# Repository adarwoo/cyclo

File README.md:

# cyclo
Author: Guillaume (Bill) ARRECKX

Brief
=====
Cyclo is a remote controllable relay capable of handling 16A over 240V AC or 3A over 120V DC.
It is housed in a DIN mountable enclosure, and offers 2 banana sockets as well as Molex connection.
It is powered through a USB socket, which also allow to drive it remotely, using a VT100 terminal.
It features a small OLED screen and a joystick to drive it manually, and display operation stats.

Intro
=====
As a professional embedded software architect, I always work on small pet
projects to keep myself up-to-date with the latest changes in languages.
This project was the perfect excuse to get to try the latest C++20 features.
Using a small, resource constrained microcontroller, is far more very
revealing of the compilers performance. 

The project initially tried to create a meta modelled framework (using concepts et al.), but
the effort required, the debug, the maintenability did not seem reasonable for now. C++20 brings
many good things, but they perform best in libraries, and should not be used solely because they
exist and are new! I also had some issues compiling existing code, so in the end, I downgraded
the project to a C++17 compiler.

Nontheless, the project features many interesting features, such as:
 * An AVR xMega (ATxMega128A4U) with 128K of flash and 8K of RAM, 2K of EEProm and a USB port
 * A XMega port of the latest FreeRTOS (10.4.4)
 * A C++ wrapper for FreeRTOS (home brew using typestrings from https://github.com/irrequietus/typestring)
 * The excellent ETL library https://www.etlcpp.com/ (I added a Tokenizer class)
 * A message framework (on top of ETL messages and FreeRTOS queues)
 * The boost::sml state machine library

Product description
===================
Cyclo can be used to cycle some systems on/off many times to validate proper boot up of embedded
equipments. It can be used to turn on/off any devices, down to 10ms to test power supplies resilence for example.
The remote control and computer friendly, and allow to control the relay directly.

The system can start automatically too.

The joystick on the side, allow configuring Cyclo manually to create a simple repeating on/off program,
with timings from 1 second to 100 minutes - on and off.

The toggle switch allow to make it normally opened or close when powered off or idle.

Up to 10 programs can be created for different scenari, single run, or repeating sequences.
When driving it from a computer, it is possible to create some custom profiles,
using random numbers, or ramps to vary the timing to look for a specific problem.

Software
========
The software architecture was done in UML, with class diagram, sequence diagram and state machines.
The emphasis is on using as much C++ as required.

No dynamic memory is used - and the stack is used as little as possible.

Building the software
=====================
The software has been written for a gcc C++17 compiler. It can be compiled
for an AVR xMega, or for a Linux PC, to run the simulator.
The need for the simulator is to allow proper debugging, which is not
possible using the Microchip Studio since the latest supported compiler is
a gcc 4.7 (the latest at the time of writting this is the 11), but to get
the c++17 feature, the compiler must be updated, and the debugging no
longer works correctly.
A makefile is also provided to compile in Linux or WSL2.
Since it uses a recent compiler, I have added a Dockerfile to create a container
to rebuild all. If you're running Linux or Windows 10/11, use the Docker container
and save yourselve plenty of pain.
A convenient script will build the docker container and launch the build.
The layout keeps the Microchip Studio layout - which is not ideal IMHO. The project can
still be opened with Microchip studio - but you'll need to ugrade the compiler.
A makefile is added to build from the command line.
The format of the files is managed by clang-format-10 which the clang config
file added.
Note: Gcc 8 or greater is required. I am using gcc 11.
I use Microsoft VSCode for all the developement - including debugging (the simulated version).
I find it is a fantastic IDE with none of the Eclipse heavyness and frustrations.
The .vs workspace is part of the distribution.

Building the hardware
=====================
The PCB can be done as a single or double sided !
Cyclo has been designed with an old Cadsoft Eagle (v7.x) using a non-profile licence.
Since, CadSoft was acquired by Autodesk, but the files remain compatible with
the latest version of Eagle. Given the size of the PCB, the free edition is enough.

I have added the .brd and .sch which must PCB house will take.
If you plan on making the PCB yourself - you will need a production method which can achieve 
at least 10mil tracks and isolation. A good CNC will do that. If you're etching, you absolutly need to
know what you're doing. This is the top end of home made PCBs, but poeple with experience can do it.
I personnaly still etch my PCB and also do PTH (Yes!). But I have a CNC for drilling, and 
a lot of chemicals like paladium... and 15 years experience doing it.

Building the case
=================
The case was designed with open source CAD and is made available as 
STL and STEP. It is 3D printer friendly.
I use a Prusa MK3 with PLA or PETG.
The PCB once cut to size will clip in place. No screews required.

Licence
=======
Cyclo is licenced under MIT licence.

External links
==============

* FreeRTOS              : https://freertos.org
* ETL                   : https://www.etlcpp.com
* Boost SML             : https://boost-ext.github.io/sml/index.html
* Typestring library    : https://github.com/irrequietus/typestring
* Toolchain for Windows : https://blog.zakkemble.net/avr-gcc-builds/
* Toolchain for Linux   : https://avr.lumito.net/downloads/
* Docker                : https://www.docker.com
* VSCode                : https://code.visualstudio.com
* Git                   : https://git-scm.com
* GNU Make              : https://www.gnu.org/software/make/
* Eagle                 : https://www.autodesk.fr/products/eagle/overview

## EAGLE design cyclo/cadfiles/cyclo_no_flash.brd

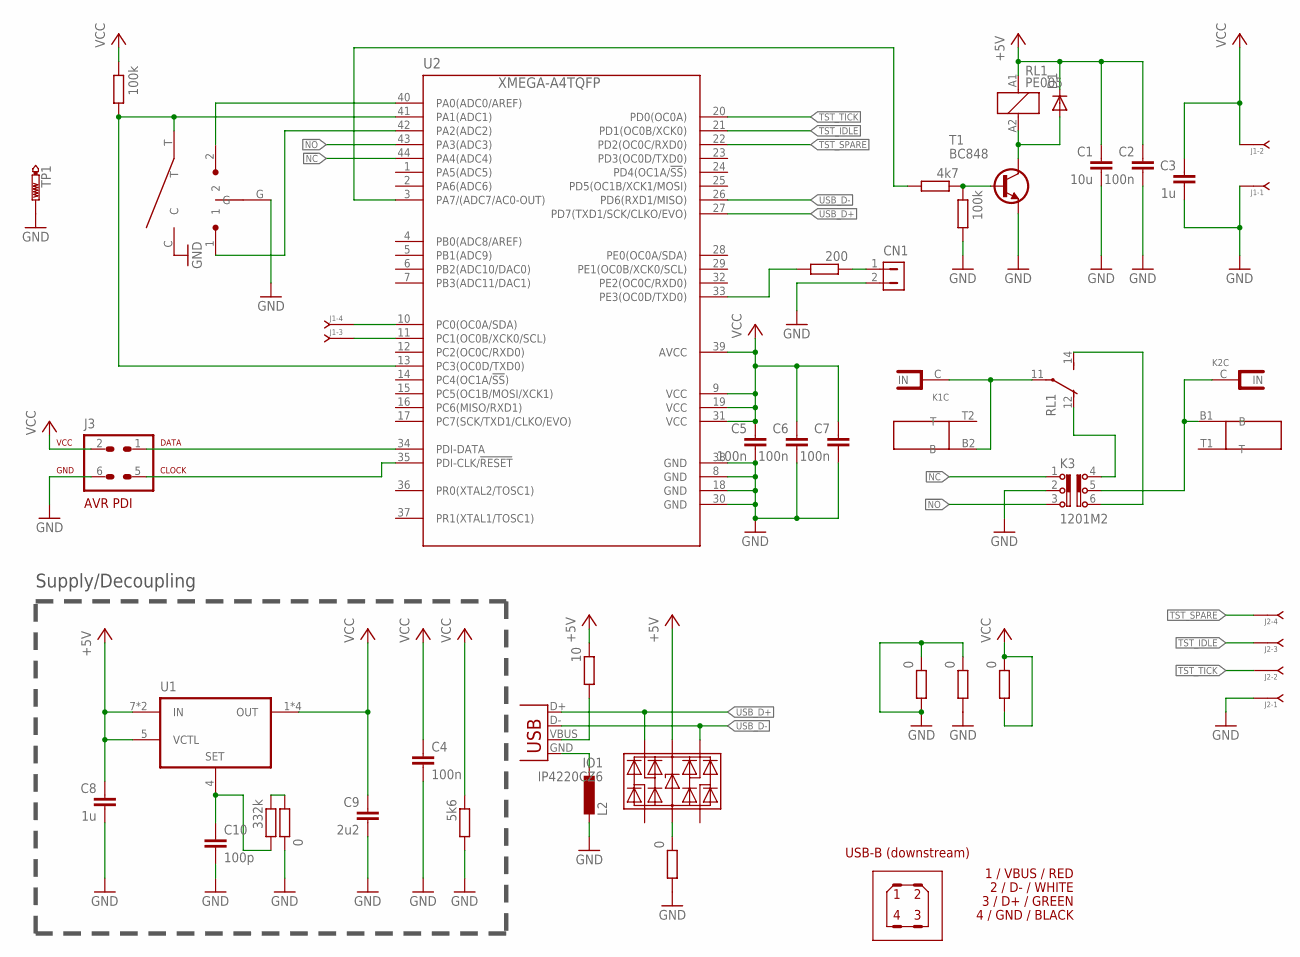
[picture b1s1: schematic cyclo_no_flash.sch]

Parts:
C1: 10u; C1210K
C2, C4, C5, C6, C7: 100n; C0603K
C3: 1u; C0603K
C8: 1u; C0805K
C9: 2u2; C0805K
C10: 100p; C0603K
CN1: HDR-1X2-70543-?; 70543-02
D1: DIODE-MINIMELF; MINIMELF
IO1: IP4220CZ6; SOT23-6
J1, J2: J-04-SIP-100; SIP-100-04
J3: AVR-PDIVERT; AVR-ISP-6
K1, K2: S16N-PCK; S16N-PC
K3: 1201M2
L2: L-EUL2012C; L2012C
R1: 4k7; R0603
R2, R4: 0; R0603
R3: 332k; R0603
R5: 5k6; R0603
R6: 200; R0603
R7: 10; R1210
R8, R11, R12: 0; R1206
R9, R10: 100k; R0603
RL1: PE005; PE
T1: BC848; SOT23
TP1: PTR1PAD1-17Y; P1-17Y
U1: LT3085; MS8E
U2: XMEGA-A4TQFP; TQFP44
U$1: H-MOLEX-2; H-MOLEX2
U$3: MCPL3BC-V; MCPL3-BC-V
X4: USB-B-H

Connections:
!NC: K3.1, U2.44 (PA4(ADC4))
!NO: K3.3, U2.43 (PA3(ADC3))
+5V: C1.1, C2.1, C8.1, D1.C, IO1.5 (UCC), R7.1, RL1.A1 (1), U1.5 (VCTL), U1.7 (IN), U1.8 (IN)
GND: C1.2, C2.2, C3.2, C4.2, C5.2, C6.2, C7.2, C8.2, C9.2, C10.2, CN1.2, J1.1, J2.1, J3.6, K3.2, L2.2, R2.1, R4.2, R5.2, R8.1, R8.2, R10.2, R11.1, R11.2, T1.2 (E), TP1.1, U2.8 (GND), U2.18 (GND), U2.30 (GND), U2.38 (GND), U$3.C, U$3.G
unnamed: IO1.2 (GND), R4.1
unnamed: U2.40 (PA0(ADC0/AREF)), U$3.2
unnamed: R6.2, U2.33 (PE3(OC0D/TXD0))
unnamed: U2.42 (PA2(ADC2)), U$3.1
unnamed: R1.2, U2.3 (PA7/(ADC7/AC0-OUT))
unnamed: R1.1, R10.1, T1.1 (B)
unnamed: K3.4, RL1.12 (O)
unnamed: K1.C (IN), RL1.11, U$1.B2 (B)
unnamed: K3.6, RL1.14 (S)
unnamed: K2.C (IN), K3.5, U$1.B1 (B)
unnamed: R2.2, R3.1
unnamed: D1.A, RL1.A2 (2), T1.3 (C)
unnamed: C10.1, R3.2, U1.4 (SET)
unnamed: CN1.1, R6.1
unnamed: R7.2, X4.VBUS
unnamed: J3.1, U2.34 (PDI-DATA)
unnamed: J3.5, U2.35 (PDI-CLK/!RESET)
unnamed: L2.1, X4.GND
PGM: R9.2, U2.13 (PC3(OC0D/TXD0)), U2.41 (PA1(ADC1)), U$3.T
SCL: J1.3, U2.11 (PC1(OC0B/XCK0/SCL))
SDA: J1.4, U2.10 (PC0(OC0A/SDA))
TST_IDLE: J2.3, U2.21 (PD1(OC0B/XCK0))
TST_SPARE: J2.4, U2.22 (PD2(OC0C/RXD0))
TST_TICK: J2.2, U2.20 (PD0(OC0A))
USB_D+: IO1.3 (B), U2.27 (PD7(TXD1/SCK/CLKO/EVO)), X4.D+
USB_D-: IO1.1 (A), U2.26 (PD6(RXD1/MISO)), X4.D-
VCC: C3.1, C4.1, C5.1, C6.1, C7.1, C9.1, J1.2, J3.2, R5.1, R9.1, R12.1, R12.2, U1.1 (OUT), U1.2 (OUT), U1.3 (OUT), U1.9 (OUT), U2.9 (VCC), U2.19 (VCC), U2.31 (VCC), U2.39 (AVCC)

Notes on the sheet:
Supply/Decoupling
1 / VBUS / RED
2 / D- / WHITE
3 / D+ / GREEN
4 / GND / BLACK
USB-B (downstream)

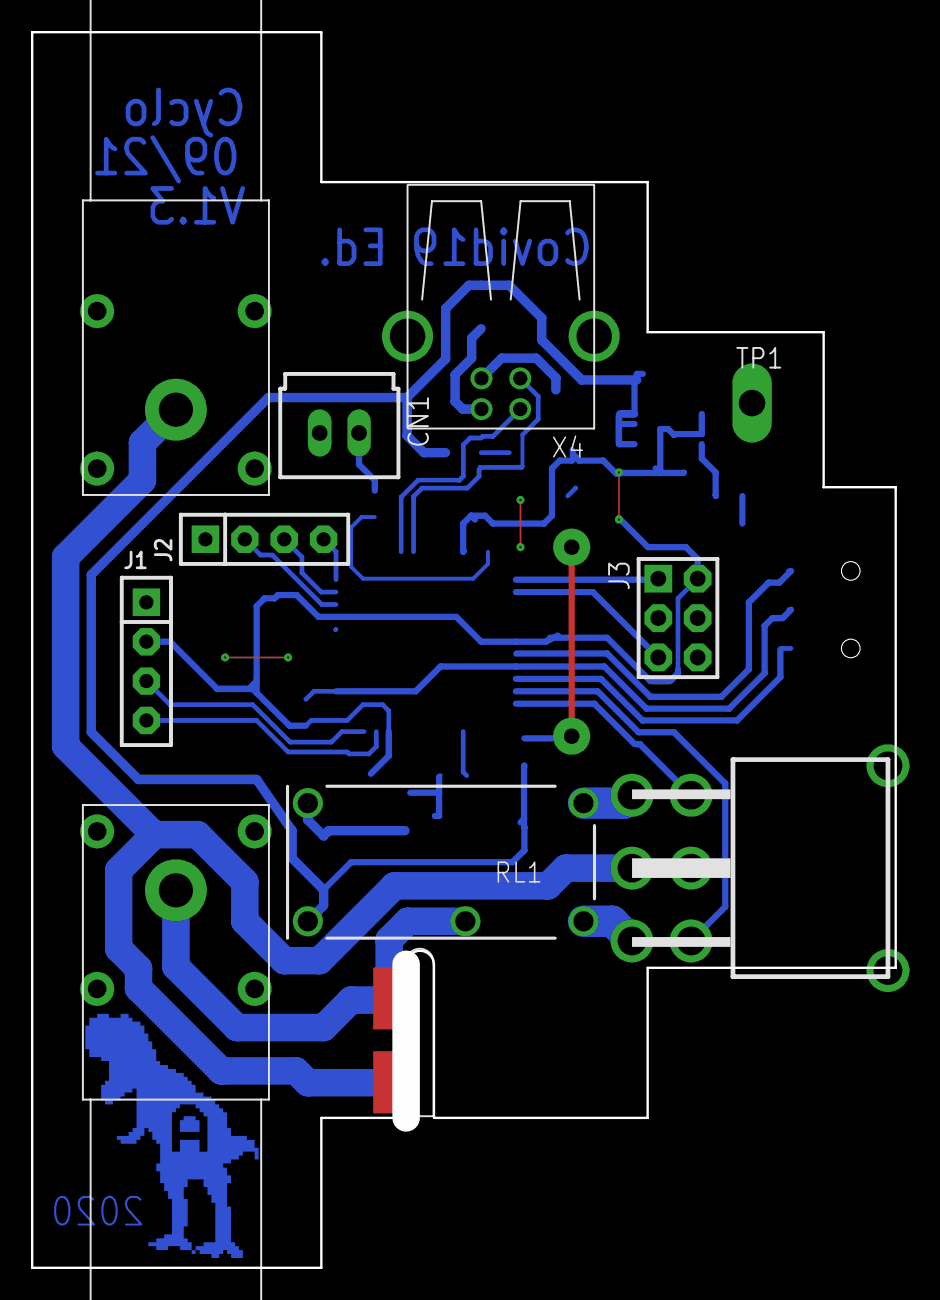
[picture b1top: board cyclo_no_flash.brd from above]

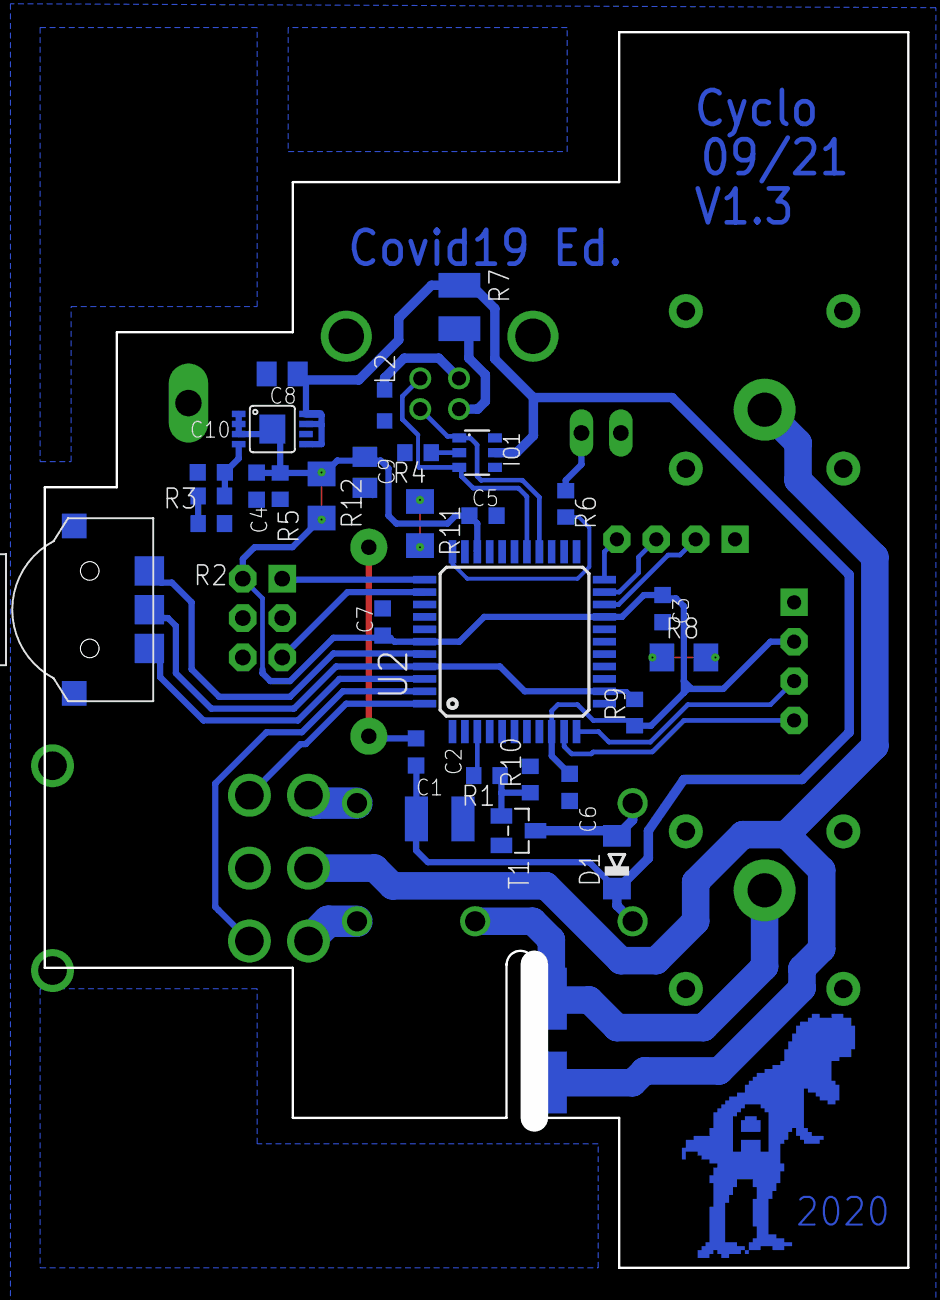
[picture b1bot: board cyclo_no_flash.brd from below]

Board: 2 copper layers, 54.1 x 78.1 mm, 40 parts (29 on the bottom side), 31 nets.

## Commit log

2021-06-30 New files
2021-07-02 New C++ task class working
2021-07-02 Adding vtask delete
2021-07-02 Moved all freertos hooks in this file
2021-07-02 latest
2021-07-02 Added comments
2021-07-03 Moving all around
2021-07-03 Task is now freertos
2021-07-03 Test task with the keypad using rtos queue
2021-07-03 Made the queue work
2021-07-03 Don't manage build dirs
2021-07-11 Adding tasklets and timers
2021-07-11 Working using the etl
2021-07-14 Not working for now
2021-07-14 Not working
2021-07-14 Seemed OK. Carefull with stack sizes
2021-07-14 Not good
2021-07-14 Good for now
2021-07-14 Before getting rid of it
2021-07-14 Graphics ok
2021-07-16 With NO/NC displayed
2021-07-16 Ignore VS code
2021-07-16 Cursor is graph. Bitmap is a pain to use
2021-07-18 Need to start working on the state machine for the HMI
2021-07-20 Working with the relay control. All messages into one package. Need SM to driver GUI
2021-08-08 More changes with the state machine working and the UI driven
2021-08-27 Full refactory to allow for Linux/WSL simulation
2021-08-27 Full refactor with libraries to allow for Linux/WSL simulation
2021-08-27 Cleanup and format
2021-08-27 Simulator getting better
2021-08-28 Renamed the Cyclo as pgm - even if to also manages the contact.
2021-08-28 Fixed a extern c. Updated projects
2021-08-28 Added view sim and fixed sm status
2021-08-28 Adjusted stack sizes
2021-08-28 Better with a lambda
2021-08-28 C++ no longer accepts register keyword
2021-08-28 Typo
2021-08-28 Time to turn on the CDC
2021-08-29 Console is alive and usb ok
2021-08-29 Cleanup sm
2021-08-29 Rename all
2021-08-29 Working renamed
2021-08-29 Rename
2021-08-30 Adding a makefile as we're going to move over to make
2021-08-30 Still working on the make
2021-08-31 Reworking the parser
2021-08-31 Almost there. Parser should be complete, list and help to do
2021-08-31 Adding dockerfile to build a docker image to build all
2021-09-01 Adding docker build
2021-09-01 Still trying to build with the makefile
2021-09-02 It links
2021-09-02 Reworking the default program
2021-09-04 Adding the copyright and MIT licence header
2021-09-05 Console basics ok
2021-09-05 Program list as save ok
2021-09-06 Update README.md
    More to come.
2021-09-07 Added the actual gfx to the lib
2021-09-07 Fixed the GUI dump
2021-09-07 Clean up
2021-09-07 X is running
2021-09-08 Fixed some bugs
2021-09-08 Working pretty well
2021-09-08 Adding the DFU firmware to flash at boot
2021-09-12 Fixed the VSCode intellisense
2021-09-12 Added repeated start to the i2c to speed up gui. Works!
2021-09-12 Reduce RAM
2021-09-17 Using a resource editor
2021-09-17 Builds ok
2021-09-17 Ignore the generated res files
2021-09-18 Using the rc resources
2021-09-18 Adding the cad and the bootloader files
2021-09-18 Minor mods. After a stop, the contact is free
2021-09-19 Moving the hack into the port macro. So it's out of the way
2021-09-19 Fixed compile error
2021-09-19 Many fixes. Handling auto last reload
2021-09-20 Minor fix to the log
2021-09-20 Tested ok on the target
2021-09-21 Testing removing virtual in tasks
2021-09-21 Added a watchdog
2023-09-17 Loop to break from in place

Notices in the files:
parts and their libraries:
con-headers-jp: Copyright (C) 2004, Bob Starr (rtzaudio@mindspring.com)
switch-ck: Copyright (C) 2011, Bob Starr
con-hdrs40: Copyright (C) 2004, Bob Starr (bobstarr@mindspring.com)
